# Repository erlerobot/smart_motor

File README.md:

# smart_servo

### ATmega 328 Microcontroller development

**AVR_OpenServo_V3** -> Stable firmware. Used to create the first prototype.

**AVR_OpenServo_V3-dev** -> Firmware under development more features than the above code.

**OpenServo_Bootloader** -> The bootloader for OpenServo proyect. It is not set in the correct memory place.

### RPI development

**RPI_SmartServo** -> Code for Raspberry Pi.

**RPI_SmartServo_Client** -> Client to send commands to the SmartServo.

**RPI_SmartServo_eagle** -> Schematics and boards for eagle SmartServo.

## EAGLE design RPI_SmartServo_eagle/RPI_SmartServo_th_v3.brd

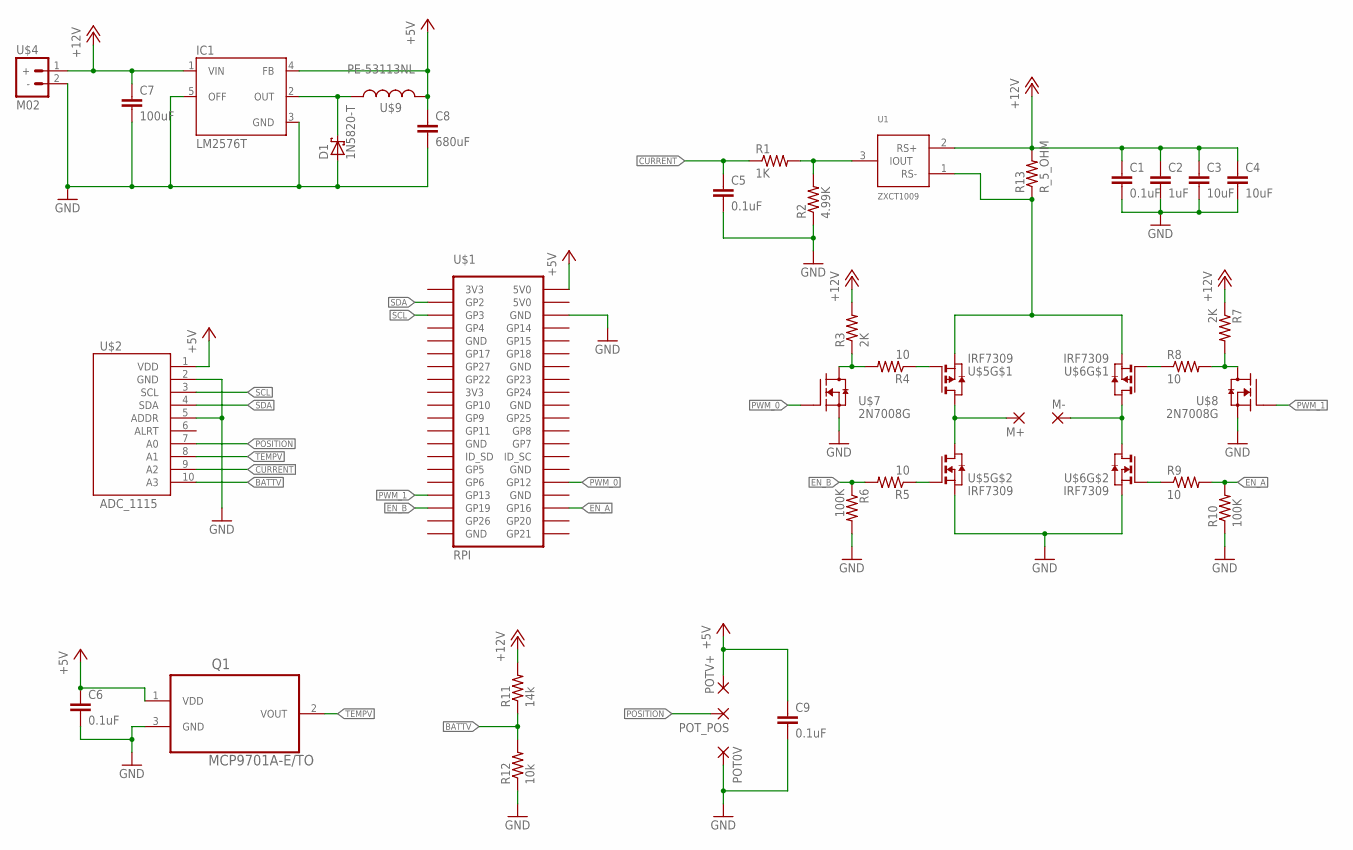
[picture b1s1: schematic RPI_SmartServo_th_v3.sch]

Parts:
C1, C5, C6, C9: 0.1uF; C025-025X050
C2: 1uF; C025-025X050
C3, C4: 10uF; C025-025X050
C7: 100uF; C025-025X050
C8: 680uF; C025-025X050
D1: 1N5820-T; C4111-15
IC1: LM2576T; TO220-5
M+: 1,6/0,9
M-: 1,6/0,9
POT0V: 1,6/0,9
POTV+: 1,6/0,9
POT_POS: 1,6/0,9
Q1: MCP9701A-E/TO; TO127P254X533-3
R1: 1K; AXIAL-0.4
R2: 4.99K; AXIAL-0.4
R3, R7: 2K; AXIAL-0.4
R4, R5, R8, R9: 10; AXIAL-0.4
R6, R10: 100K; AXIAL-0.4
R11: 14k; AXIAL-0.4
R12: 10k; AXIAL-0.4
R13: R_5_OHM; 0922/22
U1: ZXCT1009; SOT23
U$1: RPI; 2X20
U$2: ADC_1115; 1X10
U$4: M02; 1X02
U$5, U$6: IRF7309; SO8
U$7, U$8: 2N7008G; TO-92
U$9: PE-53113NL; KM-4

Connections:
+5V: C6.1, C8.1, C9.1, IC1.4 (FB), POTV+.1, Q1.1 (VDD), U$1.2 (5V0), U$2.1 (VDD), U$9.P$2 (2)
+12V: C1.1, C2.1, C3.1, C4.1, C7.1, IC1.1 (VIN), R3.P$2 (2), R7.P$1 (1), R11.P$2 (2), R13.2, U1.2 (RS+), U$4.1 (+)
BATTV: R11.P$1 (1), R12.P$2 (2), U$2.10 (A3)
CURRENT: C5.1, R1.P$1 (1), U$2.9 (A2)
EN_A: R9.P$2 (2), R10.P$2 (2), U$1.36 (GP16)
EN_B: R5.P$2 (2), R6.P$1 (1), U$1.35 (GP19)
GND: C1.2, C2.2, C3.2, C4.2, C5.2, C6.2, C7.2, C8.2, C9.2, D1.A, IC1.3 (GND), IC1.5 (OFF), POT0V.1, Q1.3 (GND), R2.P$1 (1), R6.P$2 (2), R10.P$1 (1), R12.P$1 (1), U$1.6 (GND), U$2.2 (GND), U$2.5 (ADDR), U$4.2 (-), U$5.1 (S), U$6.1 (S), U$7.1 (S), U$8.1 (S)
unnamed: R1.P$2 (2), R2.P$2 (2), U1.3 (IOUT)
unnamed: M+.1, U$5.5 (D), U$5.6 (D), U$5.7 (D), U$5.8 (D)
unnamed: R5.P$1 (1), U$5.2 (G)
unnamed: R4.P$1 (1), U$5.4 (G)
unnamed: M-.1, U$6.5 (D), U$6.6 (D), U$6.7 (D), U$6.8 (D)
unnamed: R9.P$1 (1), U$6.2 (G)
unnamed: R8.P$1 (1), U$6.4 (G)
unnamed: D1.C, IC1.2 (OUT), U$9.P$1 (1)
unnamed: R13.1, U1.1 (RS-), U$5.3 (S), U$6.3 (S)
unnamed: R3.P$1 (1), R4.P$2 (2), U$7.3 (D)
unnamed: R7.P$2 (2), R8.P$2 (2), U$8.3 (D)
POSITION: POT_POS.1, U$2.7 (A0)
PWM_0: U$1.32 (GP12), U$7.2 (G)
PWM_1: U$1.33 (GP13), U$8.2 (G)
SCL: U$1.5 (GP3), U$2.3 (SCL)
SDA: U$1.3 (GP2), U$2.4 (SDA)
TEMPV: Q1.2 (VOUT), U$2.8 (A1)

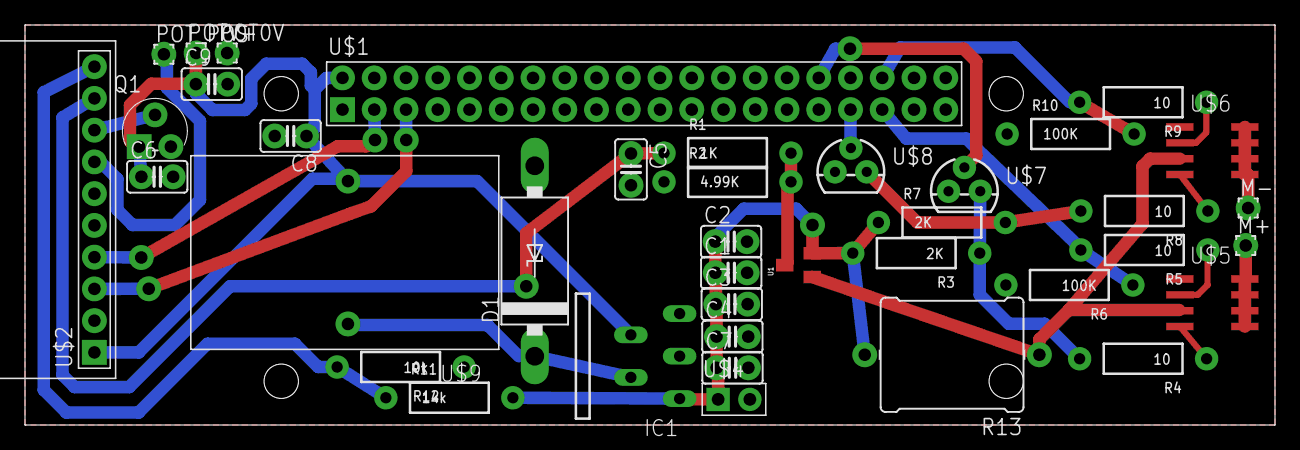
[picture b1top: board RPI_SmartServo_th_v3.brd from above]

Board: 2 copper layers, 100.0 x 32.0 mm, 39 parts (0 on the bottom side), 24 nets.

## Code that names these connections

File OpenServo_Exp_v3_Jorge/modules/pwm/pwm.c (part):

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//
//  PB1/OC1A - PWM_A    - PWM pulse output direction A
//  PB2/OC1B - PWM_B    - PWM pulse output direction B
//  PD2      - EN_A     - PWM enable direction A
//  PD3      - EN_B     - PWM enable direction B
//  PD4      - SMPLn_B  - BEMF sample enable B
//  PD7      - SMPLn_A  - BEMF sample enable A
//
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        // Set SMPLn_B (PD4) and SMPLn_A (PD7) to high.
        PORTD |= ((1<<PD4) | (1<<PD7));

        // Set EN_B (PD3) to low.
        PORTD &= ~(1<<PD3);

        // Disable PWM_A (PB1/OC1A) and PWM_B (PB2/OC1B) output.
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        // Enable PWM_A (PB1/OC1A)  output.
        TCCR1A |= (1<<COM1A1);

        // Set EN_A (PD2) to high.
        PORTD |= (1<<PD2);

        // NOTE: The PWM driven state of the H-bridge should not be switched to b-mode or braking
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        // Set SMPLn_B (PD4) and SMPLn_A (PD7) to high.
        PORTD |= ((1<<PD4) | (1<<PD7));

        // Set EN_A (PD2) to low.
        PORTD &= ~(1<<PD2);

        // Disable PWM_A (PB1/OC1A) and PWM_B (PB2/OC1B) output.
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        // Enable PWM_B (PB2/OC1B) output.
        TCCR1A = (1<<COM1B1);

        // Set EN_B (PD3) to high.
        PORTD |= (1<<PD3);

        // NOTE: The PWM driven state of the H-bridge should not be switched to a-mode or braking
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    // Initialize the pwm frequency divider value.
    pwm_div = registers_read_word(REG_PWM_FREQ_DIVIDER_HI, REG_PWM_FREQ_DIVIDER_LO);

    // Set EN_A (PD2) and EN_B (PD3) to low.
    PORTD &= ~((1<<PD2) | (1<<PD3));

    // Set SMPLn_B (PD4) and SMPLn_A (PD7) to high.
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    // top to a value lower than the counter and compare values.
    if (registers_read_word(REG_PWM_FREQ_DIVIDER_HI, REG_PWM_FREQ_DIVIDER_LO) != pwm_div)
    {
        // Hold EN_A (PD2) and EN_B (PD3) low.
        PORTD &= ~((1<<PD2) | (1<<PD3));

        // Give the H-bridge time to respond to the above, failure to do so or to wait long
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    }

    // Disable clockwise movements when position is below the minimum position.
    if ((position < min_position) && (pwm < 0)) pwm = 0;

    // Disable counter-clockwise movements when position is above the maximum position.
    if ((position > max_position) && (pwm > 0)) pwm = 0;

    // Determine if PWM is disabled in the registers.
    if (!(registers_read_byte(REG_FLAGS_LO) & (1<<FLAGS_LO_PWM_ENABLED))) pwm = 0;
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           // that has just been made.
           delay_loop(DELAYLOOP);

            // Hold EN_A (PD2) and EN_B (PD3) high.
            PORTD |= ((1<<PD2) | (1<<PD3));
        }
        else
        {
            // Hold EN_A (PD2) and EN_B (PD3) low.
            PORTD &= ~((1<<PD2) | (1<<PD3));
        }

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
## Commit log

2015-11-27 Add some structure and initial pointers for ESCs
2015-11-27 Add Open-BLDC
2015-11-28 Create dynamixel
2015-11-28 Readme.md
    # Dynamixel
2015-12-03 Add CAD
2015-12-18 OpenServo_Exp_v3_Jorge added. Code organized in modules.
2015-12-25 Some little comments in code and README for Windows10
2016-01-21 Error al compilar pwm comentadas dos lineas Añadir proyecto bootloader
2016-01-22 Cambio AVR328
2016-01-24 Cambio en twi a direccion 55. Subidos .hex, .map, .elf .lss y Makefile328
2016-01-25 OpenServo v2.8 schematic
    The schematic of the first OpenServo prototype
2016-01-28 Descomentar lineas pwm.c
2016-02-05 AVR_OpenServo_V3-dev and AVR_OpenServo_V3 added
2016-02-05 README changed
2016-02-15 Some modules ported to raspberry pi. Not compiled. Could be errors.
2016-02-16 Changes in all files and a Makefile added to be able to compile the code.
2016-02-16 Changes in code
2016-02-17 Changes in pid and pwm files. Now H bridge signals work well.
2016-03-04 modificado: RPI_SmartServo/Framework/modules/adc.c modificado: RPI_SmartServo/Framework/modules/adc.h modificado: RPI_SmartServo/Framework/modules/pid.c modificado: RPI_SmartServo/Framework/modules/p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
2016-03-04 new file: RPI_SmartServo/Framework/modules/ads1115.c new file: RPI_SmartServo/Framework/modules/ads1115.h new file: RPI_SmartServo/Framework/modules/i2c.c new file: RPI_SmartServo/Framework/modules/i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
2016-03-04 modified: Makefile modified: config.h Compilation for linux real time library -lrt in Makefile.
2016-03-06 Changes to make adc work. Changes to be committed: modified: Framework/modules/adc.c modified: Framework/modules/adc.h modified: Framework/modules/ads1115.c modified: Framework/modules/ads1115.h modi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
2016-03-06 ads1115->change in SPS defines pid -> velocity
2016-03-06 Fixe ads1115.h
2016-03-06 Change README extension
2016-03-06 Files documented for doxygen. doc folder added.
2016-03-18 modified: RPI_SmartServo/Framework/modules/ads1115.c modified: RPI_SmartServo/Framework/modules/pwm.c modified: RPI_SmartServo/main.c delay in pwm file not to burn h-bridge. proving adc, not working 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
2016-03-21 4 file added: server.c, server.h, service.c and service.h to have TCP/IP server client communication. Changes: - Create thread in main for server. - Change MSG value to uint16_t - Use register.h func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
2016-03-24 Changes to support Client server communication with servo. modified: RPI_SmartServo/Framework/modules/server.c modified: RPI_SmartServo/Makefile modified: RPI_SmartServo/main.c
2016-03-24 In previous commit also fixed ads1115 error when writing to the CONFIG register. modified: RPI_SmartServo/Framework/modules/ads1115.c
2016-03-24 Some new documentation for server and service modules. modificado: RPI_SmartServo/Framework/modules/registers.c modificado: RPI_SmartServo/Framework/modules/server.c modificado: RPI_SmartServo/Framew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
2016-03-24 Changes in ads1115 to return 12 bits values instead of 15, noise. PID and PWM configuration options moved to config file.
    modificado: RPI_SmartServo/Framework/modules/ads1115.c
    modificado: RPI_SmartServo/Framework/modules/pid.c
    modificado: RPI_SmartServo/Framework/modules/pwm.c
    modificado: RPI_SmartServo/config.h
2016-03-24 12 bits values adc modificado: RPI_SmartServo/Framework/modules/ads1115.c
2016-03-25 Change in configuration file settings. modified: RPI_SmartServo/Framework/modules/pwm.c modified: RPI_SmartServo/config.h
2016-03-25 Changes for Debugger configuration modificado: RPI_SmartServo/Framework/modules/adc.c modificado: RPI_SmartServo/Framework/modules/ads1115.c modificado: RPI_SmartServo/Framework/modules/pid.c modific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
2016-03-25 RPI servo basic working. Changed ADS delay. Changed in config the p_gain and d_gain In the main for time measure. modified: Framework/modules/ads1115.c modified: config.h modified: main.c
2016-04-10 Change in registers for current and battery. Change in config.h to support different options. Change in adc to measure current voltage and battery
    Cambios para hacer commit:
    modificado: RPI_SmartServo/Framework/modules/adc.c
    modificado: RPI_SmartServo/Framework/modules/registers.c
    modificado: RPI_SmartServo/Framework/modules/registers.h
    modificado: RPI_SmartServo/config.h
    modificado: RPI_SmartServo/main.c
2016-04-11 Added rpiservo interface abstraction for communication. Changes in adc, ads1115 and registers modifying for temperature. Cambios para hacer commit: modificado: RPI_SmartServo/Framework/modules/adc.c 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
2016-04-11 Changes in adc and ads115 to improve prototype with temp, battery and current. Changes to be committed: modified: RPI_SmartServo/Framework/modules/adc.c modified: RPI_SmartServo/Framework/modules/ads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
2016-04-11 Improving the communication interface Changes to be committed: modified: RPI_SmartServo/Framework/modules/adc.c modified: RPI_SmartServo/Framework/modules/ads1115.c modified: RPI_SmartServo/Framework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
2016-04-15 Changes to support new communication interface. Cambios para hacer commit: modificado: RPI_SmartServo/Framework/modules/adc.c modificado: RPI_SmartServo/Framework/modules/ads1115.c modificado: RPI_Sm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
2016-04-28 Eagle files uploaded new file: RPI_SmartServo_eagle/RPI_SmartServo_th.brd new file: RPI_SmartServo_eagle/RPI_SmartServo_th.sch
2016-04-28 Ground plane added modificado: RPI_SmartServo_eagle/RPI_SmartServo_th.brd
2016-04-28 Changed the Current Sensor modificado: RPI_SmartServo_eagle/RPI_SmartServo_th.brd modificado: RPI_SmartServo_eagle/RPI_SmartServo_th.sch
2016-05-04 New board and schematics files. new file: RPI_SmartServo_eagle/RPI_SmartServo_th_v2.brd new file: RPI_SmartServo_eagle/RPI_SmartServo_th_v2.sch
2016-05-10 Added RPI_Smart_Servo_Client
    new file: RPI_SmartServo_Client/README.txt
    new file: RPI_SmartServo_Client/client.c
    new file: RPI_SmartServo_Client/service.h
2016-05-10 Changes for new interface: modified: RPI_SmartServo/Framework/modules/ads1115.c modified: RPI_SmartServo/Framework/modules/rpiservo.c modified: RPI_SmartServo/Framework/modules/rpiservo.h modified: R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
2016-05-14 Change in RPI_SmartServo_th_v2.brd modificado: RPI_SmartServo_eagle/RPI_SmartServo_th_v2.brd
2016-05-14 Deleted OpenServo_Exp_v3_Jorge
2016-05-14 Update README.md
    Added RPI_Smart_Servo_Client and eagle. Deleted OpenServo_Jorge_dev
2016-05-16 Timer code to probe ADS1115
2016-05-16 Changes to be committed: modified: Makefile modified: Timer.c
2016-05-17 Add make clean in the makefile to erase de .o files.
2016-05-17 Documentation update
2016-05-17 Cambios para hacer commit: modificado: Timer/src/Makefile
2016-05-17 New board v3 with wider paths and reorganized new file: RPI_SmartServo_eagle/RPI_SmartServo_th_v3.brd new file: RPI_SmartServo_eagle/RPI_SmartServo_th_v3.sch
2016-05-30 modified: RPI_SmartServo/config.h
2016-06-06 Add some anotations to sch
2016-06-06 Change Mains printfs
2016-06-06 Add Basic Integrer function to PID
2016-06-07 PID: Add first read position as the init pos
2016-06-07 Registers: Add first read position as first pos to seek
2016-06-07 Main: Change initialization process to first read initial pos
2016-06-08 Add antiwindup Integral in PID
2016-06-09 Main: fix compilation errors
2016-06-09 R11 and R12 voltage divider in software
2016-06-17 Change printfs
2016-06-19 Main: print degree conversion

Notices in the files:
OpenServo_Exp_v3_Jorge/modules/pwm/pwm.c:
Copyright (c) 2006 Michael P. Thompson <mpthompson@gmail.com>
parts and their libraries:
SparkFun-Resistors: Licensing: Creative Commons ShareAlike 4.0 International - https://creativecommons.org/licenses/by-sa/4.0
